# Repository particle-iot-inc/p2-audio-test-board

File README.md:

This is a schematic for the P2 that shows how to incorporate PDM and I2S codecs into the P2 / Photon 2 and M-SoM platform.

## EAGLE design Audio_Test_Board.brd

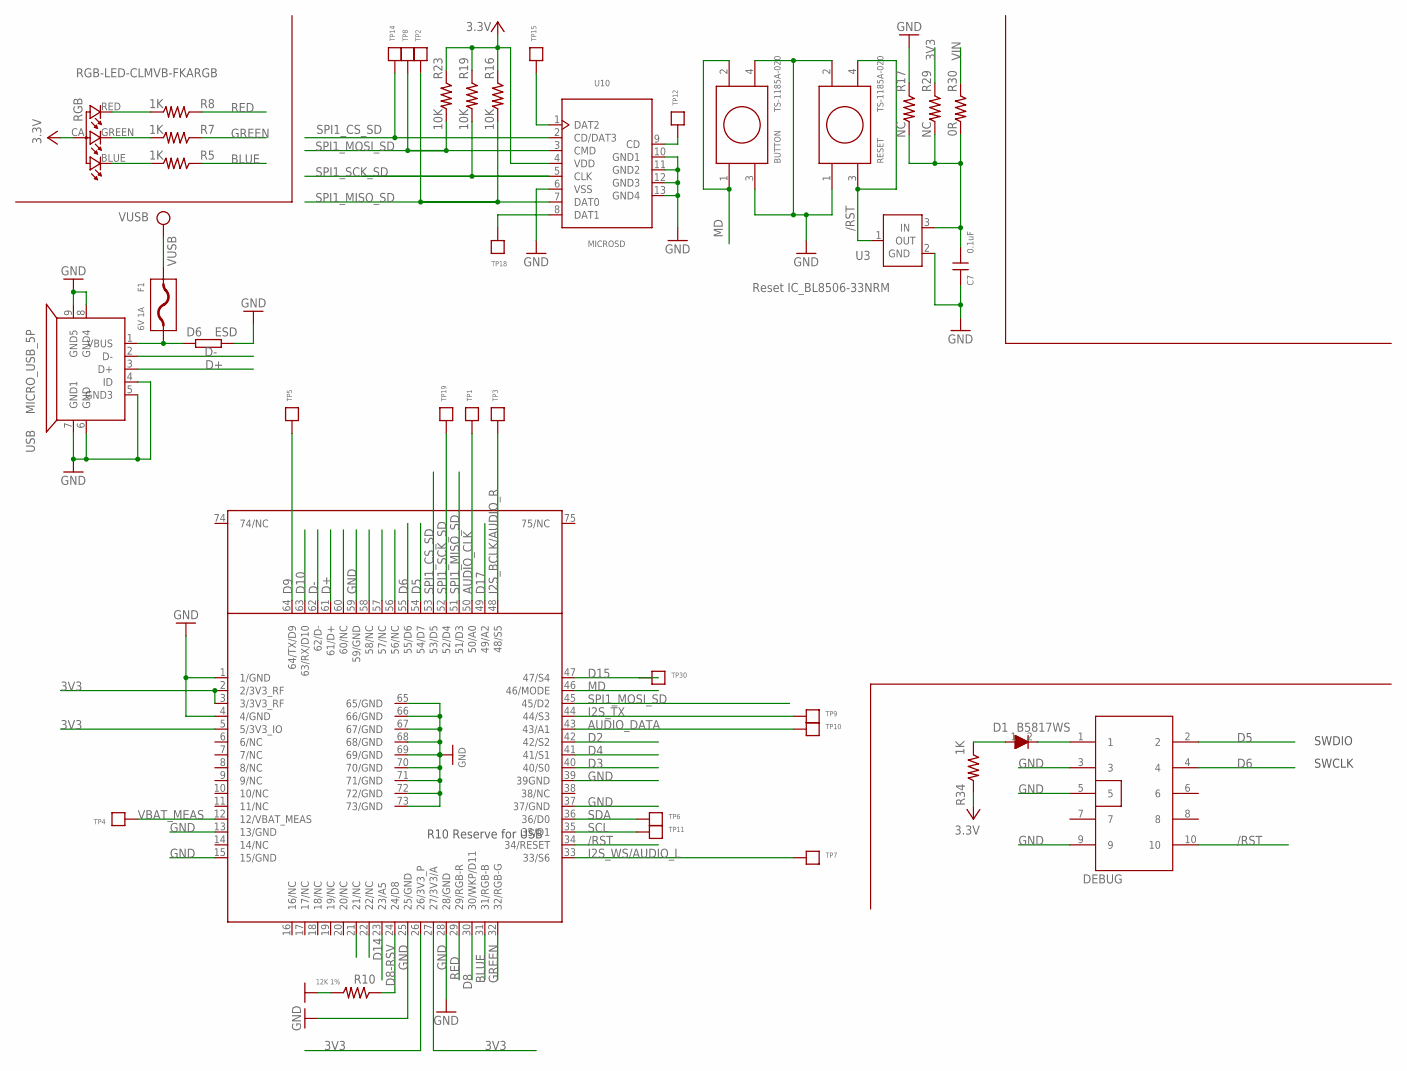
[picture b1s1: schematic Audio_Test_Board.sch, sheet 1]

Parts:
BUTTON: TS-1185A-020
C7: 0.1uF; C-0402
D1: B5817WS; SOD-323
D6: ESD; R-0402S
DEBUG: CON5X2; CON5X2_1.27
F1: 6V 1A; F0805
P2: TRON
R5, R7, R8, R34: 1K; R-0402S
R10: 12K 1%; R-0402S
R16, R19, R23: 10K; R-0402S
R17, R29: NC; R-0402S
R30: 0R; R-0402S
RESET: TS-1185A-020
RGB: RGB-LED-CLMVB-FKARGB; PLCC4-2MM-RGB
TP1, TP2, TP3, TP4, TP5, TP6, TP7, TP8, TP9, TP10, TP11, TP12, TP14, TP15, TP18, TP19, TP30: TP; TP0.7MM
U3: Reset IC_BL8506-33NRM; PARTICLE-SZ_SOT-23
U10: MICROSD
USB: MICRO_USB_5P; MICRO_USB

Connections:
3V3: P2.2 (2/3V3_RF), P2.3 (3/3V3_RF), P2.5 (5/3V3_IO), P2.26 (26/3V3_P), P2.27 (27/3V3/A), R16.1, R19.1, R23.1, R29.1, R34.2, RGB.CA (1), U10.4 (VDD); also elsewhere on the board
/RST: DEBUG.10, P2.34 (34/RESET), RESET.3, RESET.4, U3.1 (OUT)
AUDIO_CLK: P2.50 (50/A0), TP1.P$1; also elsewhere on the board
AUDIO_DATA: P2.43 (43/A1), TP10.P$1; also elsewhere on the board
BLUE: P2.31 (31/RGB-B), R5.1
D2: P2.42 (42/S2)
D3: P2.40 (40/S0)
D4: P2.41 (41/S1)
D5: DEBUG.2, P2.54 (54/D7)
D6: DEBUG.4, P2.55 (55/D6)
D8: P2.30 (30/WKP/D11)
D8-RSV: P2.24 (24/D8), R10.1
D9: P2.64 (64/TX/D9), TP5.P$1
D10: P2.63 (63/RX/D10)
D14: P2.23 (23/A5)
D15: P2.47 (47/S4), TP30.P$1
D17: P2.49 (49/A2)
D+: P2.61 (61/D+), USB.3 (D+)
D-: P2.62 (62/D-), USB.2 (D-)
GND: BUTTON.3, BUTTON.4, C7.2, D6.1, DEBUG.3, DEBUG.5, DEBUG.9, P2.1 (1/GND), P2.4 (4/GND), P2.13 (13/GND), P2.15 (15/GND), P2.25 (25/GND), P2.28 (28/GND), P2.37 (37/GND), P2.39 (39GND), P2.59 (59/GND), P2.65 (65/GND), P2.66 (66/GND), P2.67 (67/GND), P2.68 (68/GND), P2.69 (69/GND), P2.70 (70/GND), P2.71 (71/GND), P2.72 (72/GND), P2.73 (73/GND), R10.2, R17.1, RESET.1, RESET.2, U3.2 (GND), U10.6 (VSS), U10.10 (GND1), U10.11 (GND2), U10.12 (GND3), U10.13 (GND4), USB.4 (ID), USB.5 (GND3), USB.6 (GND), USB.7 (GND1), USB.8 (GND4), USB.9 (GND5); also elsewhere on the board
GREEN: P2.32 (32/RGB-G), R7.1
I2S_BCLK/AUDIO_R: P2.48 (48/S5), TP3.P$1; also elsewhere on the board
I2S_TX: P2.44 (44/S3), TP9.P$1; also elsewhere on the board
I2S_WS/AUDIO_L: P2.33 (33/S6), TP7.P$1; also elsewhere on the board
MD: BUTTON.1, BUTTON.2, P2.46 (46/MODE)
unnamed: D1.1, R34.1
unnamed: D1.2, DEBUG.1
unnamed: TP12.P$1, U10.9 (CD)
unnamed: D6.2, F1.P$1 (1), USB.1 (VBUS)
unnamed: R8.2, RGB.RED (4)
unnamed: R5.2, RGB.BLUE (2)
unnamed: R7.2, RGB.GREEN (3)
unnamed: TP15.P$1, U10.1 (DAT2)
unnamed: TP18.P$1, U10.8 (DAT1)
unnamed: C7.1, R17.2, R29.2, R30.2, U3.3 (IN)
RED: P2.29 (29/RGB-R), R8.1
SCL: P2.35 (35/D1), TP11.P$1
SDA: P2.36 (36/D0), TP6.P$1
SPI1_CS_SD: P2.53 (53/D5), TP14.P$1, U10.2 (CD/DAT3)
SPI1_MISO_SD: P2.51 (51/D3), R16.2, TP2.P$1, U10.7 (DAT0)
SPI1_MOSI_SD: P2.45 (45/D2), R23.2, TP8.P$1, U10.3 (CMD)
SPI1_SCK_SD: P2.52 (52/D4), R19.2, TP19.P$1, U10.5 (CLK)
VBAT_MEAS: P2.12 (12/VBAT_MEAS), TP4.P$1
VIN: R30.1; also elsewhere on the board
VUSB: F1.P$2 (2); also elsewhere on the board

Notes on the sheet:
SWCLK
SWDIO
R10 Reserve for USB

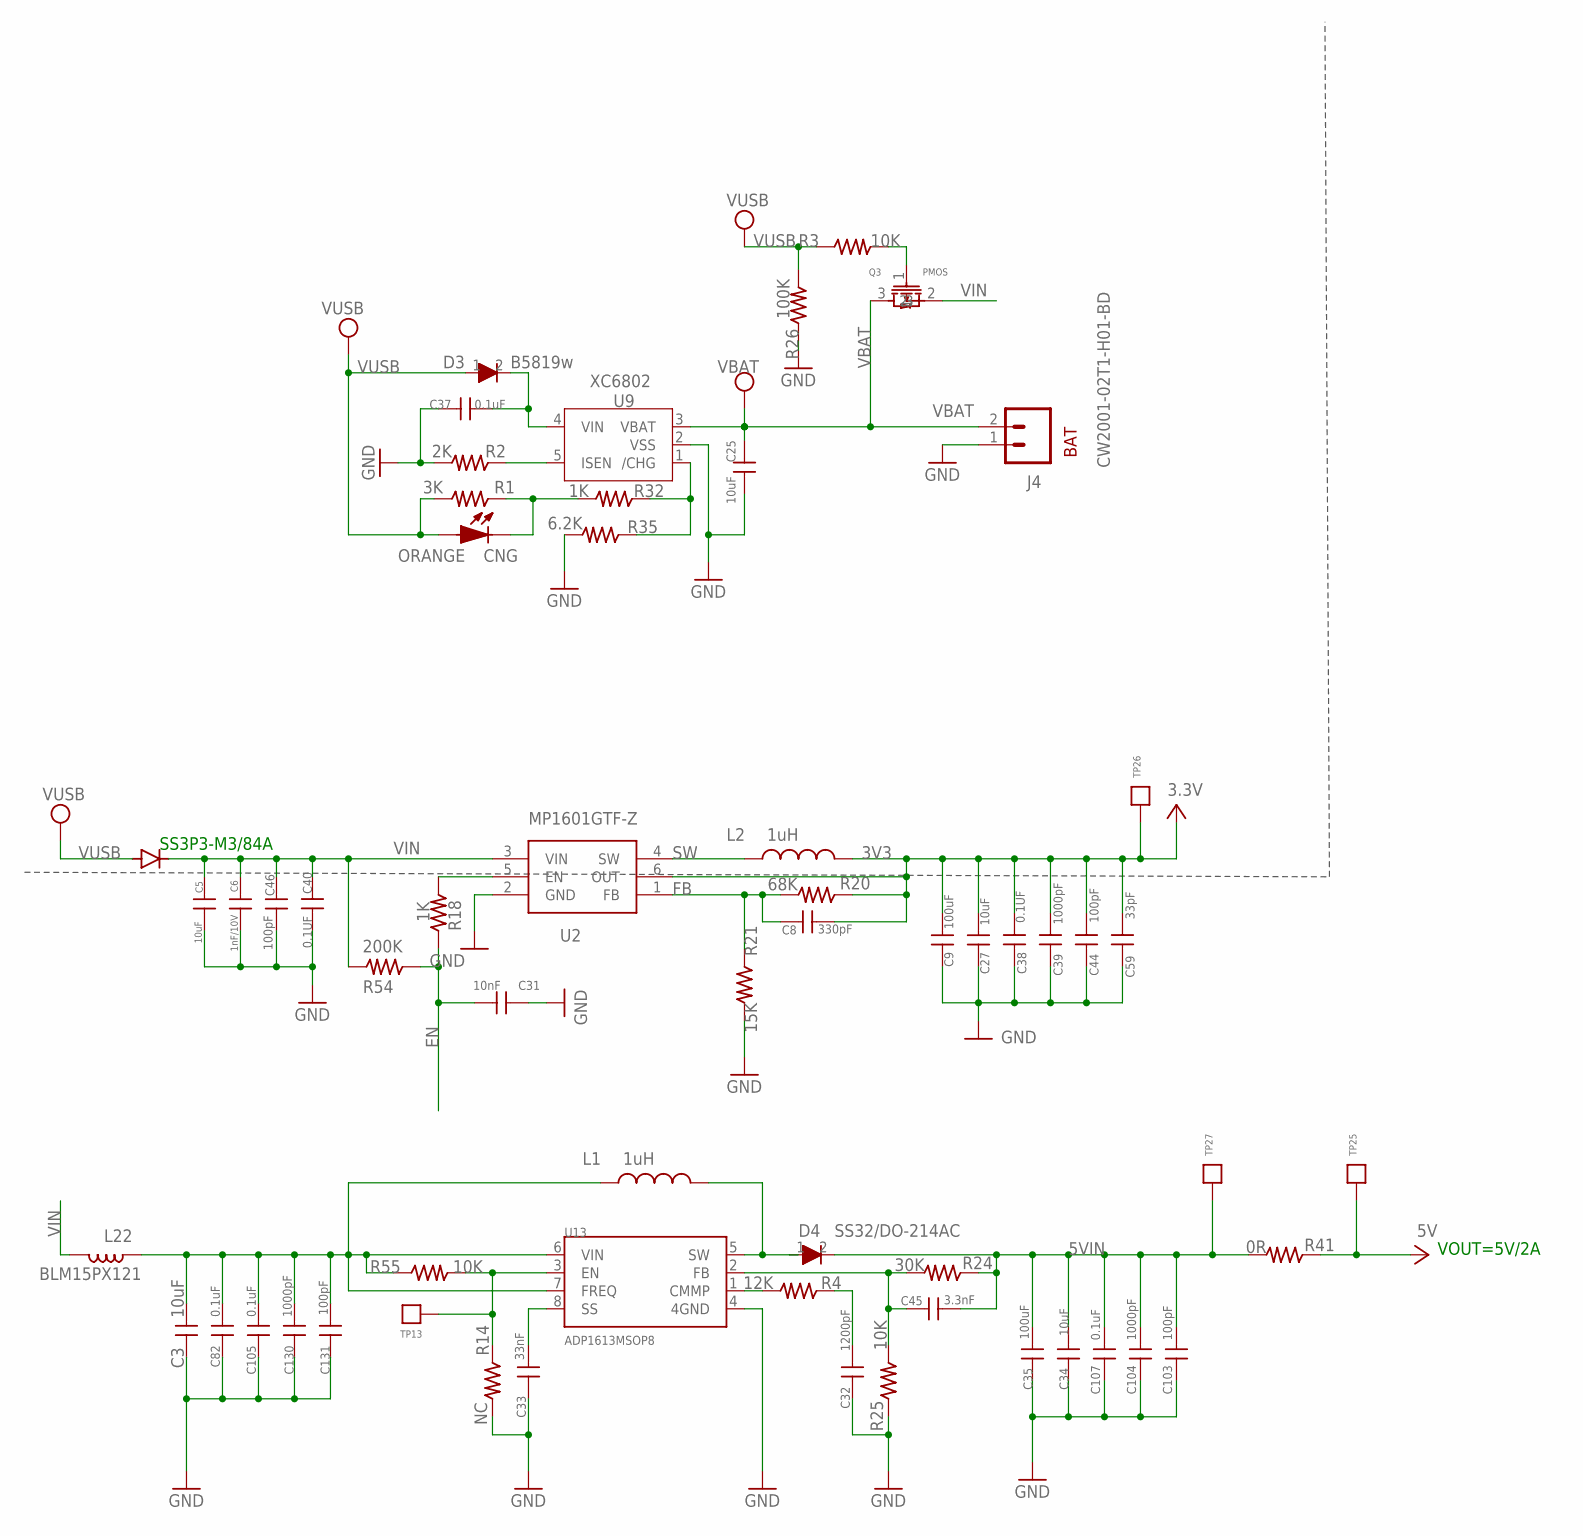
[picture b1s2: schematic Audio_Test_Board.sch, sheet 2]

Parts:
C3, C5, C27, C34: 10uF; C0603
C6: 1nF/10V; C-0402
C8: 330pF; C0402
C9, C35: 100uF; C1206
C25: 10uF; C0805
C31: 10nF; C-0402
C32: 1200pF; C-0402
C33: 33nF; C-0402
C37, C107: 0.1uF; C-0402
C38, C40: 0.1UF; C-0402
C39, C104: 1000pF; C-0402
C44, C46, C103, C131: 100pF; C-0402
C45: 3.3nF; C0402
C59: 33pF; C-0402
C82, C105: 0.1uF; C0402
C130: 1000pF; C0402
CNG: ORANGE; LED0603
D2: SS3P3-M3/84A; DIODE-DO-220AA_NT(SMP)
D3: B5819w; SOD-123
D4: SS32/DO-214AC; DO-214AC
J4: CW2001-02T1-H01-BD; JST-2-SMD
L1, L2: 1uH; INDUCTOR-VLS-E
L22: BLM15PX121; R-0402S
Q3: PMOS; SOT-23
R1: 3K; R-0402S
R2: 2K; R-0402S
R3, R25, R55: 10K; R-0402S
R4: 12K; R-0402S
R14: NC; R-0402S
R18, R32: 1K; R-0402S
R20: 68K; R-0402S
R21: 15K; R-0402S
R24: 30K; R-0402S
R26: 100K; R-0402S
R35: 6.2K; R-0402S
R41: 0R; R1206
R54: 200K; R-0402S
TP13, TP25, TP26, TP27: TP; TP0.7MM
U2: MP1601GTF-Z; SOTFL50P160X60-6N
U9: XC6802; SOT-23-5
U13: ADP1613MSOP8; MSOP8

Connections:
3V3: C8.2, C9.1, C27.1, C38.2, C39.2, C44.2, C59.2, L2.P$2 (2), R20.1, TP26.P$1, U2.6 (OUT); also elsewhere on the board
5V: R41.1, TP25.P$1; also elsewhere on the board
5VIN: C34.1, C35.1, C45.2, C103.1, C104.1, C107.1, D4.2, R24.1, R41.2, TP27.P$1
CH: R32.1, R35.1, U9.1 (/CHG)
EN: C31.2, R18.1, R54.1
FB: C8.1, R20.2, R21.1, U2.1 (FB)
GND: C3.2, C5.2, C6.2, C9.2, C25.1, C27.2, C31.1, C32.2, C33.2, C34.2, C35.2, C37.2, C38.1, C39.1, C40.1, C44.1, C46.2, C59.1, C82.2, C103.2, C104.2, C105.2, C107.2, C130.2, C131.2, J4.1 (2), R2.2, R14.2, R21.2, R25.1, R26.1, R35.2, U2.2 (GND), U9.2 (VSS), U13.4 (4GND); also elsewhere on the board
unnamed: R2.1, U9.5 (ISEN)
unnamed: C33.1, U13.8 (SS)
unnamed: C32.1, R4.1
unnamed: R18.2, U2.5 (EN)
unnamed: D4.1, L1.P$2 (2), U13.5 (SW)
unnamed: R14.1, R55.2, TP13.P$1, U13.3 (EN)
unnamed: Q3.1, R3.2
unnamed: C37.1, D3.2, U9.4 (VIN)
unnamed: CNG.2 (K), R1.1, R32.2
unnamed: C45.1, R24.2, R25.2, U13.2 (FB)
unnamed: R4.2, U13.1 (CMMP)
unnamed: C3.1, C82.1, C105.1, C130.1, C131.1, L1.P$1 (1), L22.1, R55.1, U13.6 (VIN), U13.7 (FREQ)
SW: L2.P$1 (1), U2.4 (SW)
VBAT: C25.2, J4.2 (1), Q3.3, U9.3 (VBAT)
VIN: C5.1, C6.1, C40.2, C46.1, D2.CATHODE, L22.2, Q3.2, R54.2, U2.3 (VIN); also elsewhere on the board
VUSB: CNG.1 (A), D2.ANODE, D3.1, R1.2, R3.1, R26.2; also elsewhere on the board

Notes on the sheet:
SS3P3-M3/84A
VOUT=5V/2A
BAT

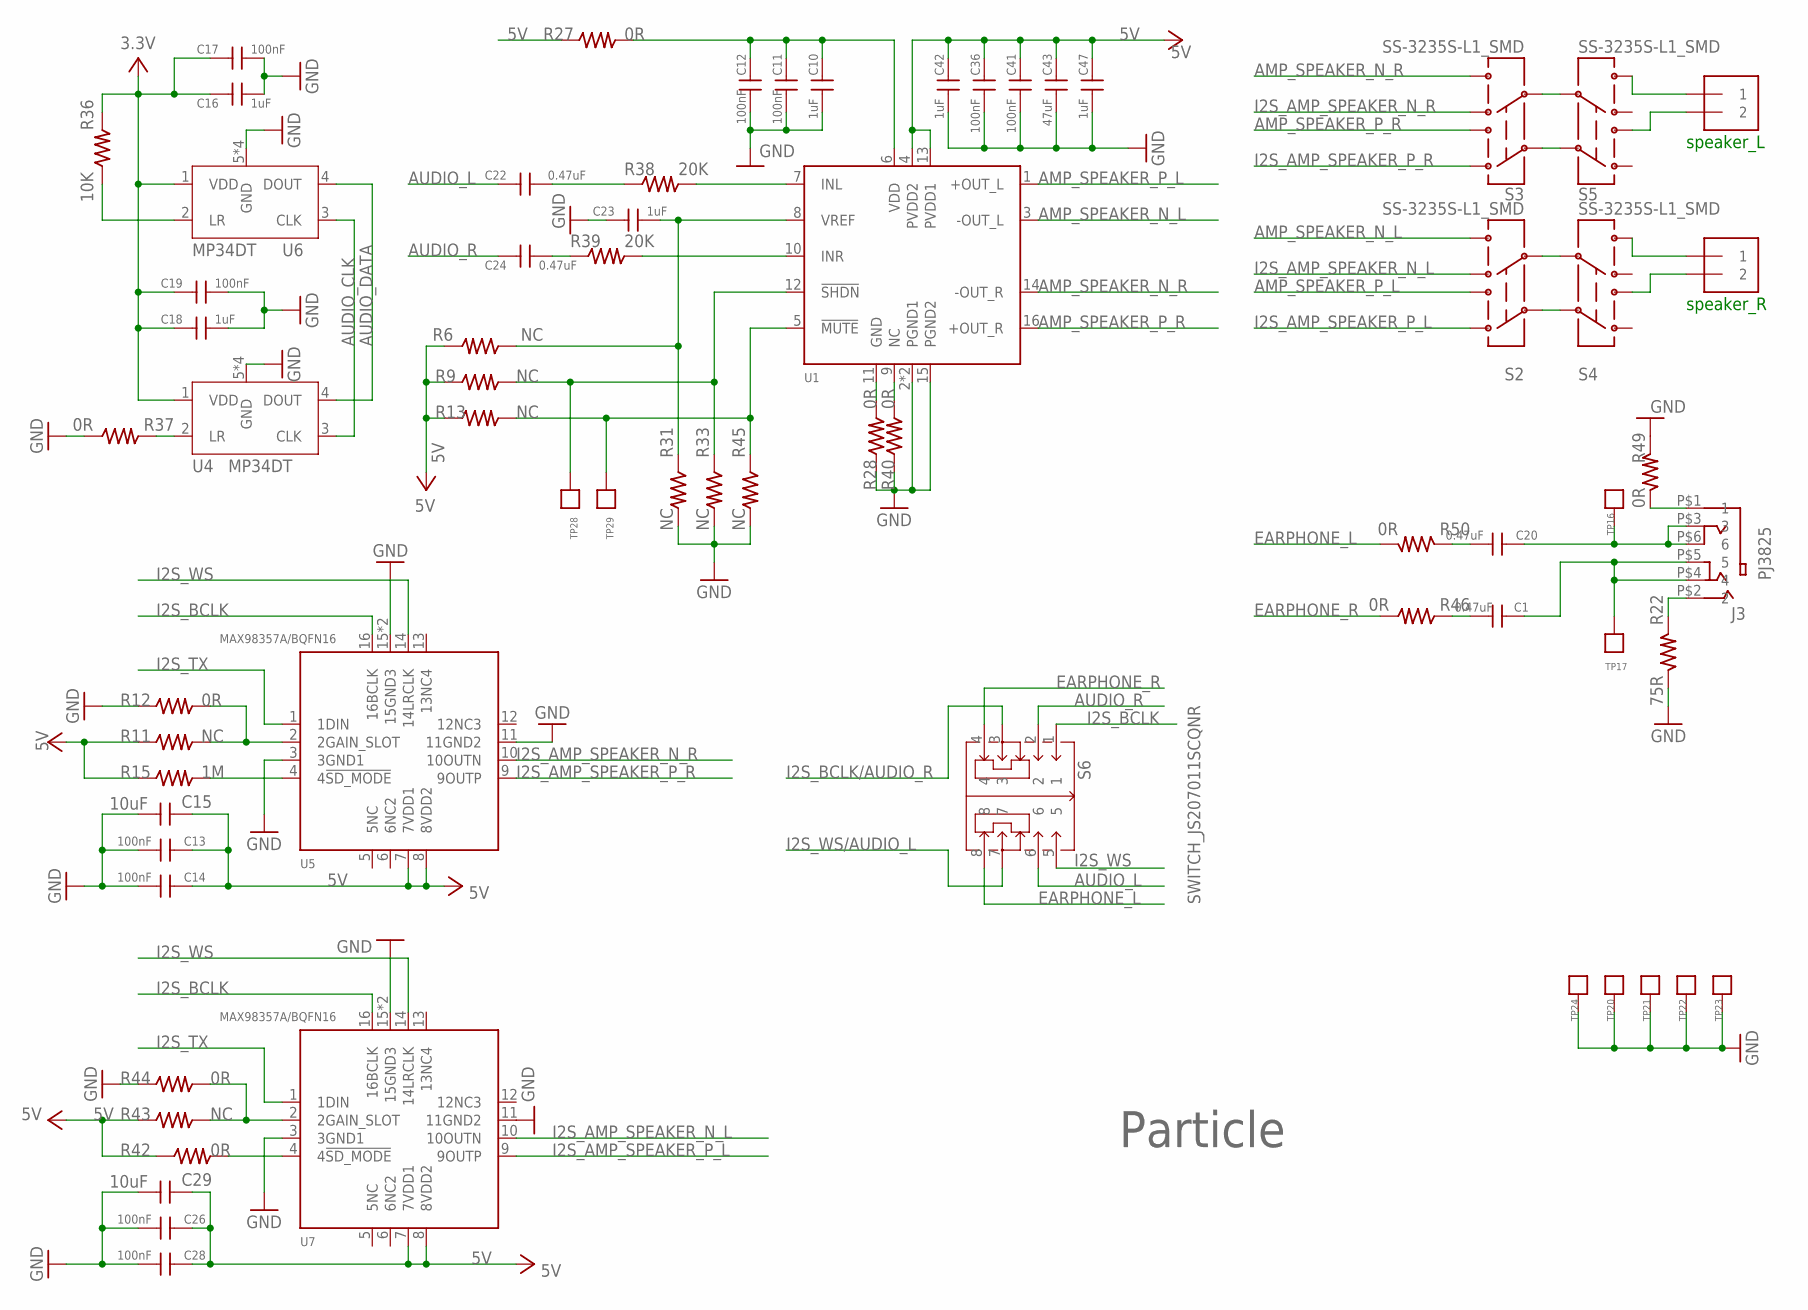
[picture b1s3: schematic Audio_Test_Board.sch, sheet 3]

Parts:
C1, C20: 0.47uF; C0805
C10, C16, C18, C23, C42, C47: 1uF; C-0402
C11, C12, C13, C14, C17, C19, C26, C28, C36, C41: 100nF; C-0402
C15, C29: 10uF; C0603
C22, C24: 0.47uF; C-0402
C43: 47uF; C1206
J1, J2: 1X2-3.5MM
J3: PJ3825
R6, R9, R11, R13, R31, R33, R43, R45: NC; R-0402S
R12, R27, R28, R37, R40, R42, R44: 0R; R-0402S
R15: 1M; R-0402S
R22: 75R; R-0402S
R36: 10K; R-0402S
R38, R39: 20K; R-0402S
R46, R49, R50: 0R; R0805
S2, S3, S4, S5: SS-3235S-L1_SMD
S6: SWITCH_JS207011SCQNR; SWITCH-JS207011SCQNR
TP16, TP17, TP20, TP21, TP22, TP23, TP24, TP28, TP29: TP; TP0.7MM
U1: PARTICLE-SZ_PAM8403DRSOP16; PARTICLE-SZ_SOIC16
U4, U6: MP34DT
U5, U7: MAX98357A/BQFN16; QFN16

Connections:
3V3: C16.2, C17.2, C18.2, C19.2, R36.2, U4.1 (VDD), U6.1 (VDD); also elsewhere on the board
5V: C13.2, C14.2, C15.1, C26.2, C28.2, C29.1, C36.2, C41.2, C42.2, C43.2, C47.2, R6.2, R9.1, R11.1, R13.1, R15.1, R27.1, R42.1, R43.1, U1.4 (PVDD2), U1.13 (PVDD1), U5.7 (7VDD1), U5.8 (8VDD2), U7.7 (7VDD1), U7.8 (8VDD2); also elsewhere on the board
AMP_SPEAKER_N_L: S2.4, U1.3 (-OUT_L)
AMP_SPEAKER_N_R: S3.4, U1.14 (-OUT_R)
AMP_SPEAKER_P_L: S2.1, U1.1 (+OUT_L)
AMP_SPEAKER_P_R: S3.1, U1.16 (+OUT_R)
AUDIO_CLK: U4.3 (CLK), U6.3 (CLK); also elsewhere on the board
AUDIO_DATA: U4.4 (DOUT), U6.4 (DOUT); also elsewhere on the board
AUDIO_L: C22.2, S6.6
AUDIO_R: C24.2, S6.2
EARPHONE_L: R50.2, S6.8
EARPHONE_R: R46.2, S6.4
GND: C10.1, C11.1, C12.1, C13.1, C14.1, C15.2, C16.1, C17.1, C18.1, C19.1, C23.2, C26.1, C28.1, C29.2, C36.1, C41.1, C42.1, C43.1, C47.1, R12.1, R22.1, R28.1, R31.2, R33.2, R37.1, R40.1, R44.1, R45.2, R49.2, TP20.P$1, TP21.P$1, TP22.P$1, TP23.P$1, TP24.P$1, U1.2 (PGND1), U1.15 (PGND2), U1.THERM (PGND1), U4.5 (GND), U4.6 (GND), U4.7 (GND), U4.8 (GND), U5.3 (3GND1), U5.11 (11GND2), U5.15 (15GND3), U5.TH (15GND3), U6.5 (GND), U6.6 (GND), U6.7 (GND), U6.8 (GND), U7.3 (3GND1), U7.11 (11GND2), U7.15 (15GND3), U7.TH (15GND3); also elsewhere on the board
I2S_AMP_SPEAKER_N_L: S2.6, U7.10 (10OUTN)
I2S_AMP_SPEAKER_N_R: S3.6, U5.10 (10OUTN)
I2S_AMP_SPEAKER_P_L: S2.3, U7.9 (9OUTP)
I2S_AMP_SPEAKER_P_R: S3.3, U5.9 (9OUTP)
I2S_BCLK: S6.1, U5.16 (16BCLK), U7.16 (16BCLK)
I2S_BCLK/AUDIO_R: S6.3; also elsewhere on the board
I2S_TX: U5.1 (1DIN), U7.1 (1DIN); also elsewhere on the board
I2S_WS: S6.5, U5.14 (14LRCLK), U7.14 (14LRCLK)
I2S_WS/AUDIO_L: S6.7; also elsewhere on the board
unnamed: R13.2, R45.1, TP29.P$1, U1.5 (!MUTE)
unnamed: R9.2, R33.1, TP28.P$1, U1.12 (!SHDN)
unnamed: C23.1, R6.1, R31.1, U1.8 (VREF)
unnamed: S3.5, S5.5
unnamed: R11.2, R12.2, U5.2 (2GAIN_SLOT)
unnamed: J1.2, S4.1
unnamed: J2.2, S5.1
unnamed: R37.2, U4.2 (LR)
unnamed: C24.1, R39.1
unnamed: S3.2, S5.2
unnamed: R38.2, U1.7 (INL)
unnamed: J2.1, S5.4
unnamed: R15.2, U5.4 (4!SD_MODE)
unnamed: J3.P$2 (2), R22.2
unnamed: R39.2, U1.10 (INR)
unnamed: C1.1, R46.1
unnamed: R36.1, U6.2 (LR)
unnamed: R40.2, U1.9 (NC)
unnamed: C10.2, C11.2, C12.2, R27.2, U1.6 (VDD)
unnamed: R28.2, U1.11 (GND)
unnamed: C20.2, J3.P$3 (3), J3.P$6 (6), TP16.P$1
unnamed: C22.1, R38.1
unnamed: C1.2, J3.P$4 (4), J3.P$5 (5), TP17.P$1
unnamed: S2.5, S4.5
unnamed: S2.2, S4.2
unnamed: R42.2, U7.4 (4!SD_MODE)
unnamed: R43.2, R44.2, U7.2 (2GAIN_SLOT)
unnamed: J1.1, S4.4
unnamed: J3.P$1 (1), R49.1
unnamed: C20.1, R50.1

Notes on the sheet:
Particle
speaker_L
speaker_R

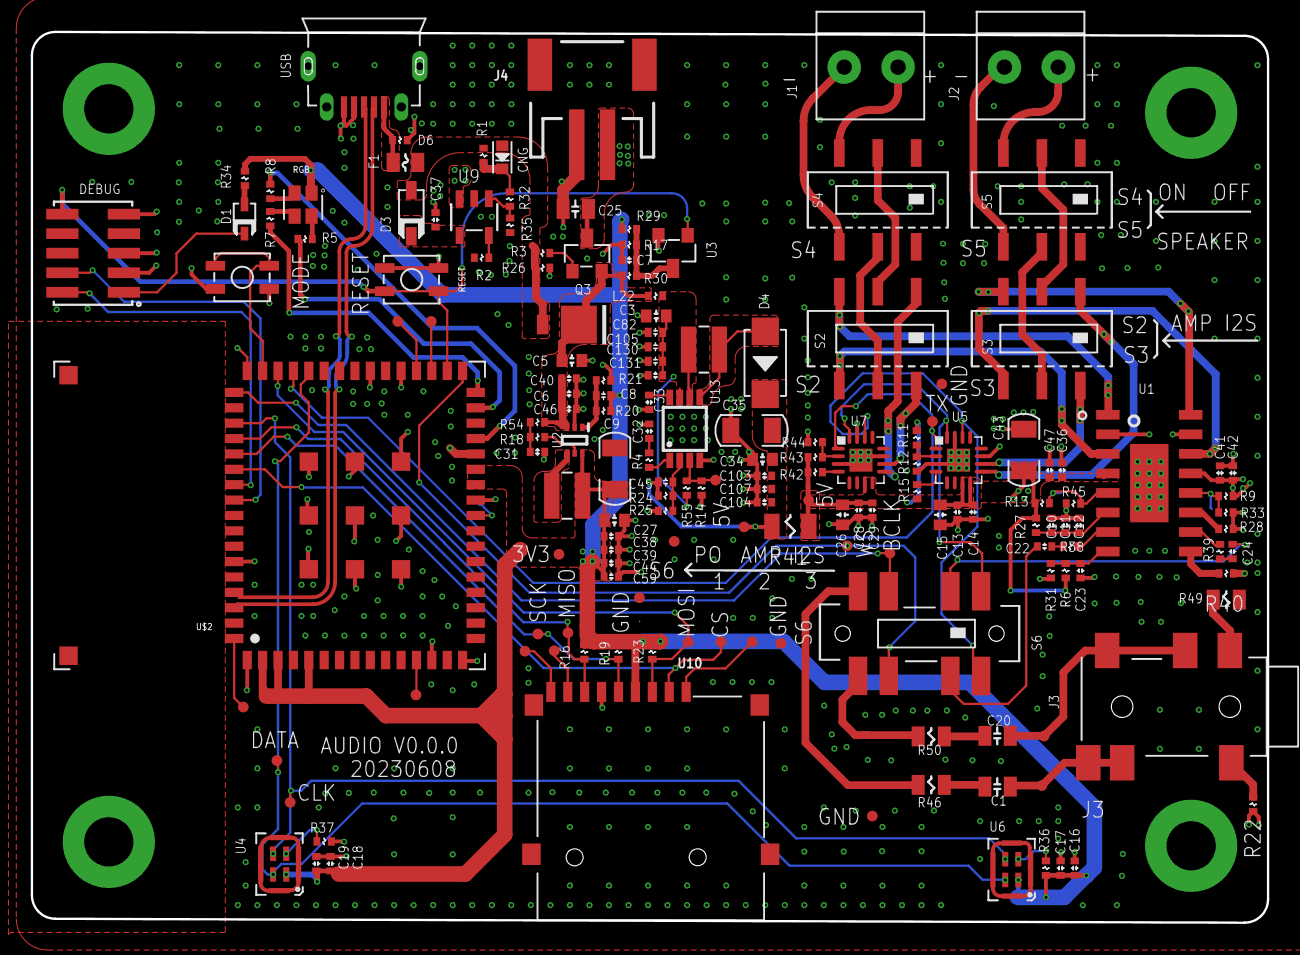
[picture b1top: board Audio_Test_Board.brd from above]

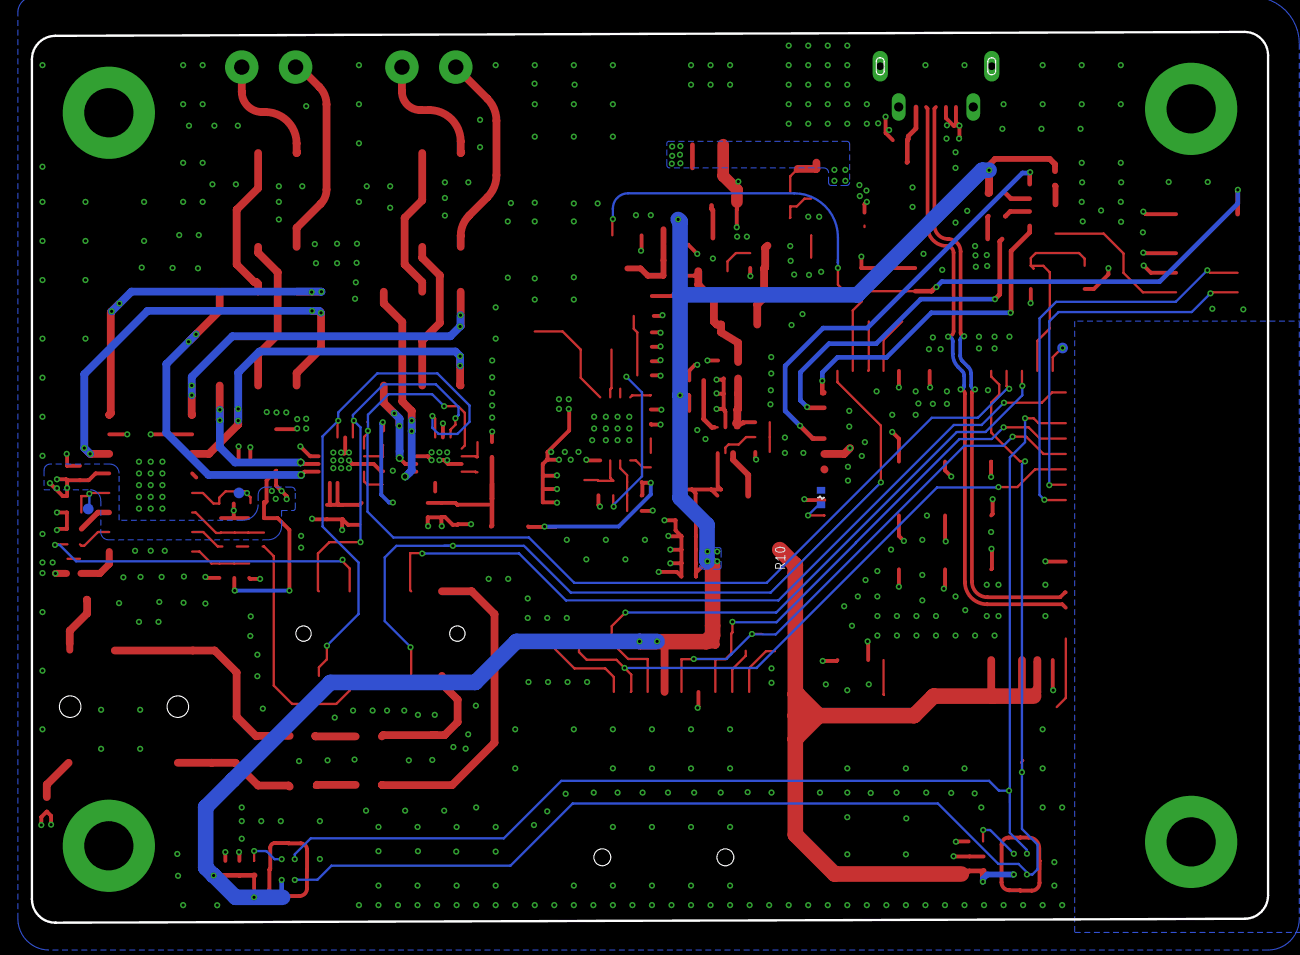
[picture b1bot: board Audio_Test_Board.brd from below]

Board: 4 copper layers, 80.4 x 57.9 mm, 168 parts (4 on the bottom side), 101 nets.

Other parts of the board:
LOGO: PARTICLE-LOGO

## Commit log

2024-07-18 update the pdf
    update the pdf
2025-08-20 Add CC-BY-SA license

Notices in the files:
parts and their libraries:
SparkFun-Connectors: Licensing: Creative Commons ShareAlike 4.0 International - https://creativecommons.org/licenses/by-sa/4.0
